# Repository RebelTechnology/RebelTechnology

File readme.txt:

Base repository for Rebel Technology electronics projects.

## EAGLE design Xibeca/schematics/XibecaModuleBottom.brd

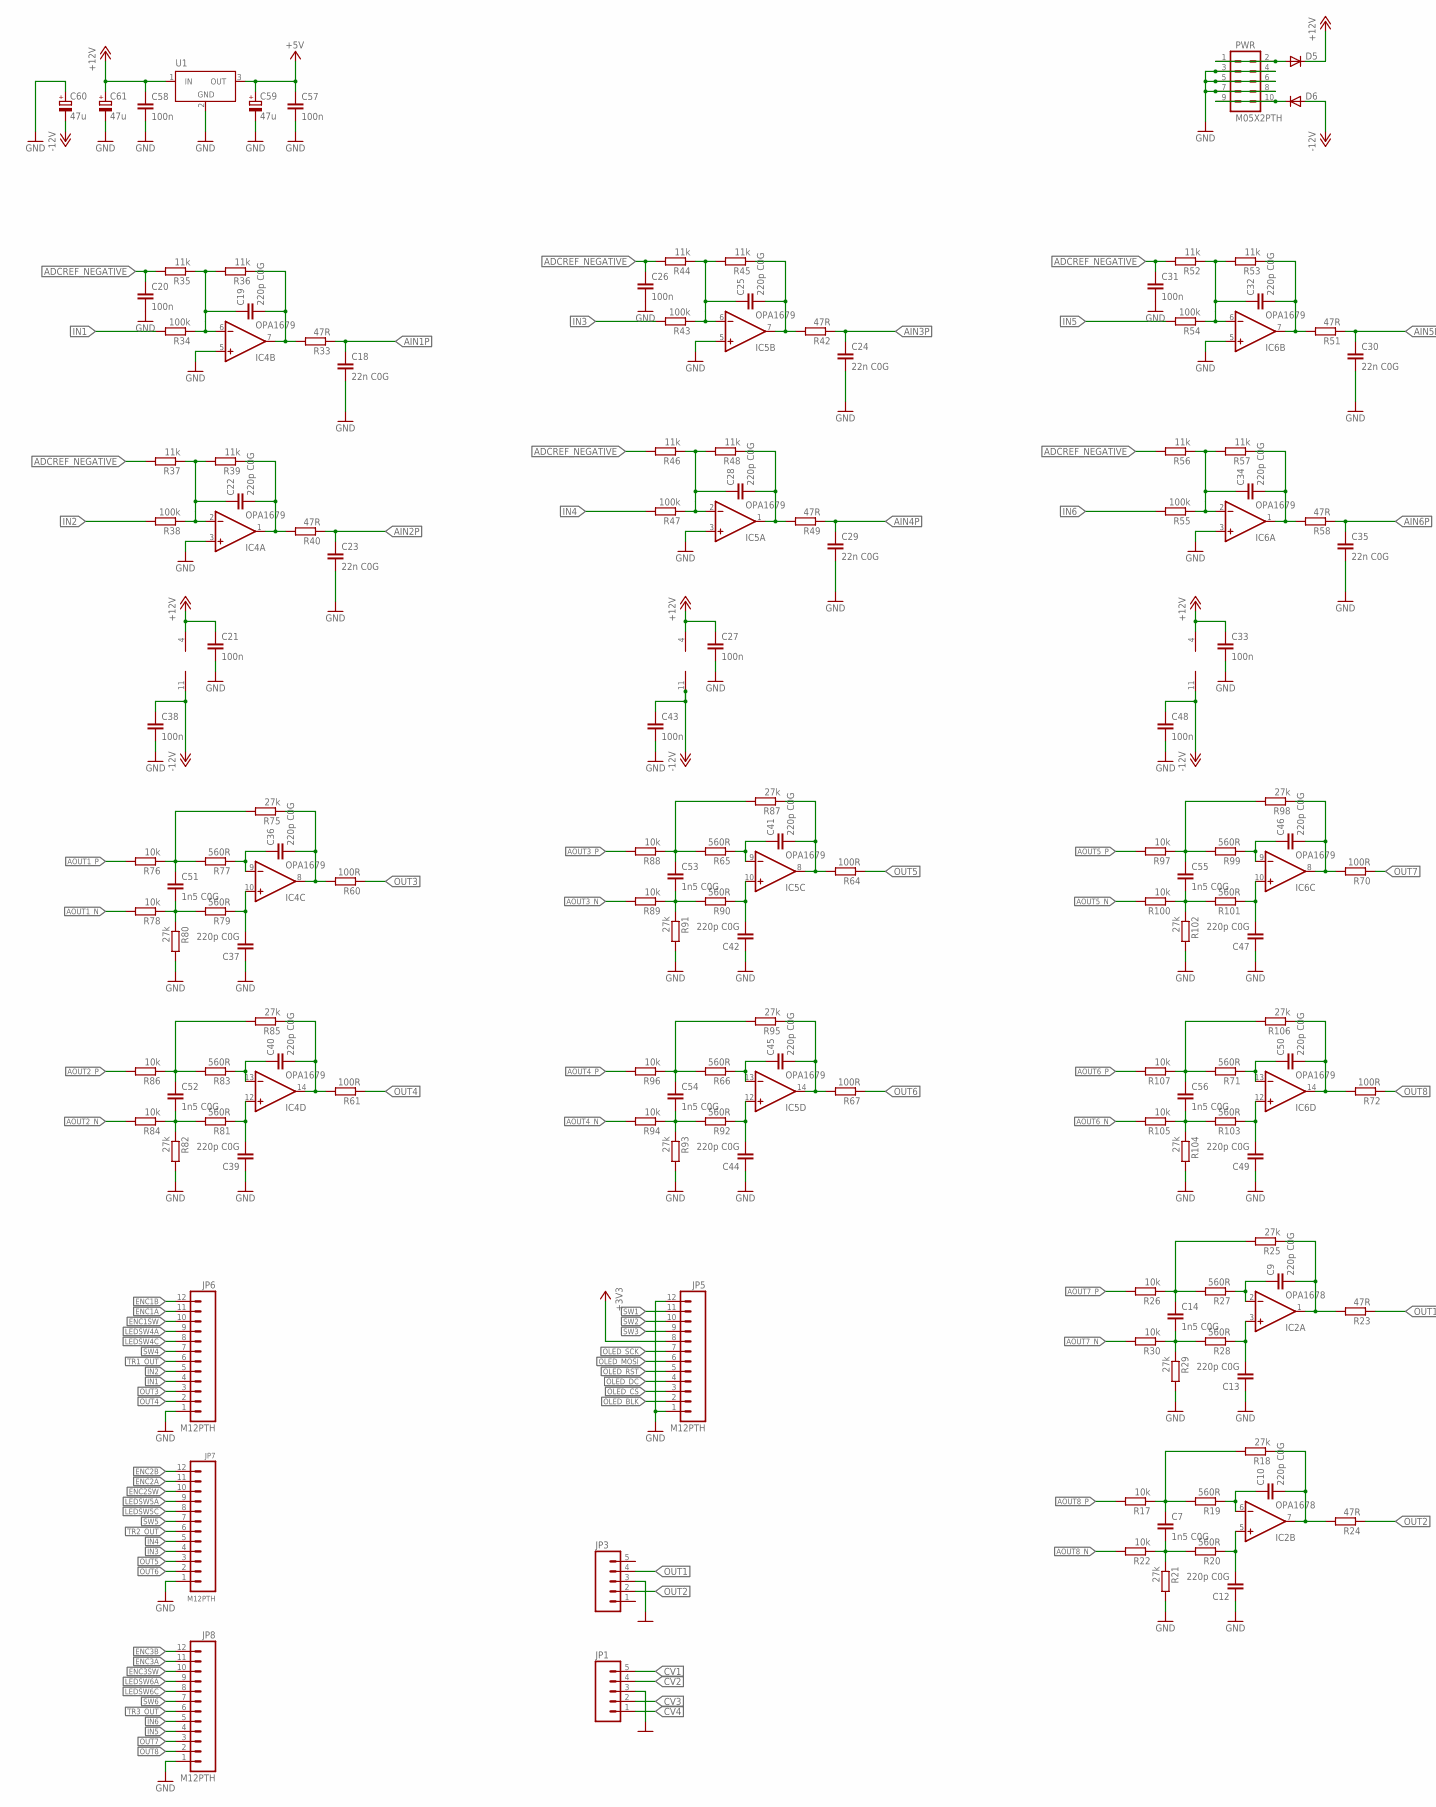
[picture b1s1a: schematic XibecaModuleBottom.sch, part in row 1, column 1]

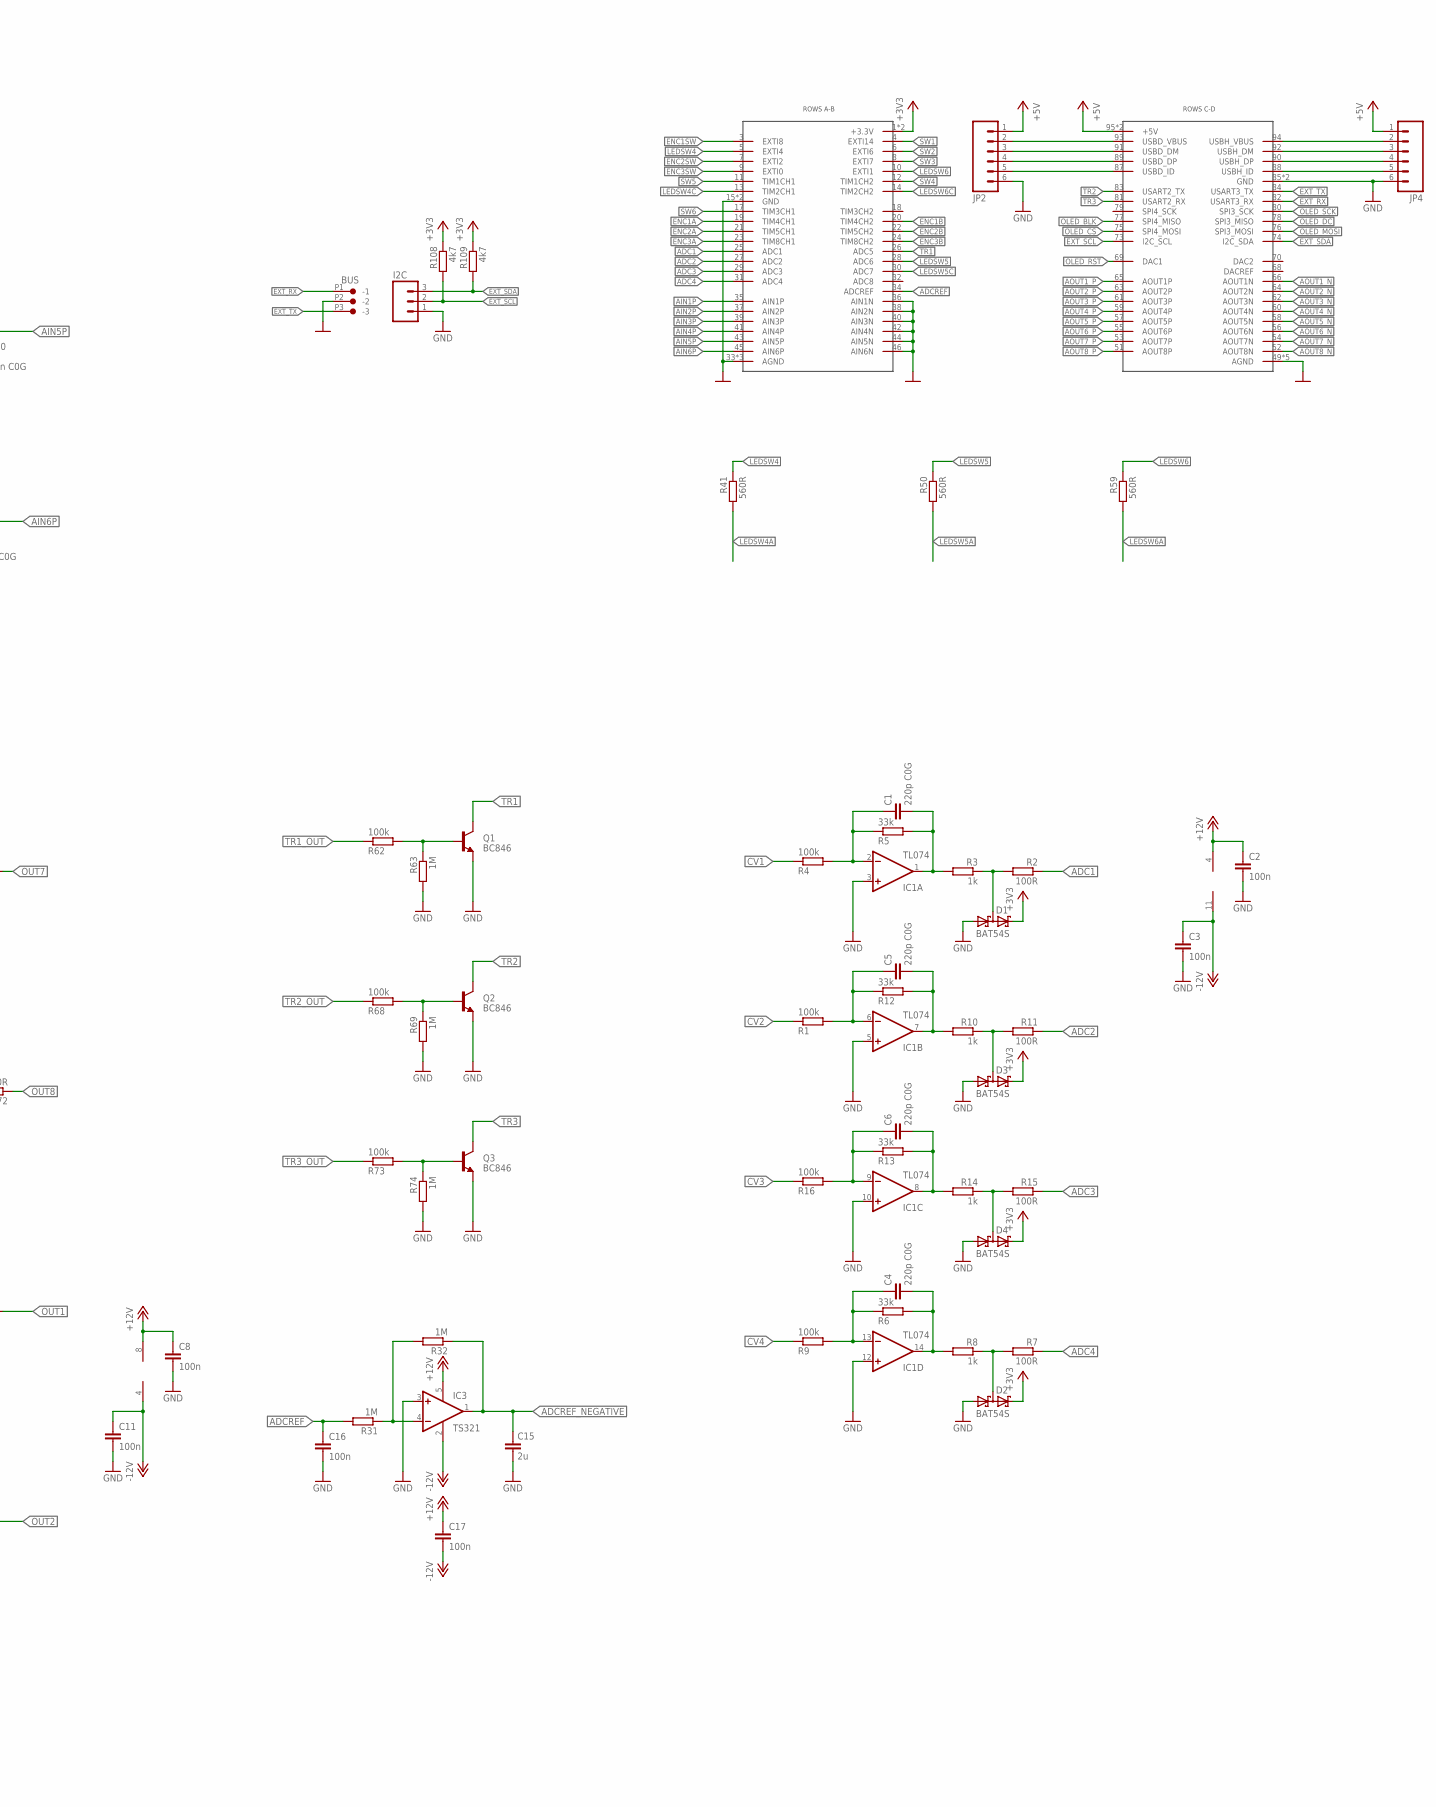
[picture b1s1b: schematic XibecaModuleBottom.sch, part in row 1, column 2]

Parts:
BUS: CON-JST_PH_3W
C1, C4, C5, C6, C9, C10, C12, C13, C19, C22, C25, C28, C32, C34, C36, C37, C39, C40, C41, C42, C44, C45, C46, C47, C49, C50: 220p C0G; C0603
C2, C3, C8, C11, C16, C17, C20, C21, C26, C27, C31, C33, C38, C43, C48, C57, C58: 100n; C0603
C7, C14, C51, C52, C53, C54, C55, C56: 1n5 C0G; C0603
C15: 2u; C0603
C18, C23, C24, C29, C30, C35: 22n C0G; C0603
C59, C60, C61: 47u; E5-8,5
D1, D2, D3, D4: BAT54S; SOT23
D5, D6: DIODE1N4001; DIODE-1N4001
I2C: M03PTH; 1X03
IC1: TL074; SO14
IC2: OPA1678; SO08
IC3: TS321; SOT23-5
IC4, IC5, IC6: OPA1679; SO14
JP1, JP3: M05PTH; 1X05
JP2, JP4: M06SIP; 1X06
JP5, JP6, JP7, JP8: M12PTH; 1X12
PWR: M05X2PTH; AVR_ICSP
Q1, Q2, Q3: BC846; SOT23
R1, R4, R9, R16, R34, R38, R43, R47, R54, R55, R62, R68, R73: 100k; 0603
R2, R7, R11, R15, R60, R61, R64, R67, R70, R72: 100R; 0603
R3, R8, R10, R14: 1k; 0603
R5, R6, R12, R13: 33k; 0603
R17, R22, R26, R30, R76, R78, R84, R86, R88, R89, R94, R96, R97, R100, R105, R107: 10k; 0603
R18, R21, R25, R29, R75, R80, R82, R85, R87, R91, R93, R95, R98, R102, R104, R106: 27k; 0603
R19, R20, R27, R28, R41, R50, R59, R65, R66, R71, R77, R79, R81, R83, R90, R92, R99, R101, R103: 560R; 0603
R23, R24, R33, R40, R42, R49, R51, R58: 47R; 0603
R31, R32, R63, R69, R74: 1M; 0603
R35, R36, R37, R39, R44, R45, R46, R48, R52, R53, R56, R57: 11k; 0603
R108, R109: 4k7; 0603
U1: TSR-1-2450
U$2: NOCTUA2NOCTUA2; NOCTUA

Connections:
+3V3: D1.2 (C2), D2.2 (C2), D3.2 (C2), D4.2 (C2), JP5.8, R108.1, R109.1, U$2.1 (+3.3V), U$2.2 (+3.3V)
+5V: C57.1, C59.+, JP2.1, JP4.1, U1.3 (OUT), U$2.95 (+5V), U$2.96 (+5V)
+12V: C2.1, C8.1, C17.1, C21.1, C27.1, C33.1, C58.1, C61.+, D5.C, IC1.4 (V+), IC2.8 (V+), IC3.5 (V+), IC4.4 (V+), IC5.4 (V+), IC6.4 (V+), U1.1 (IN)
-12V: C3.1, C11.1, C17.2, C38.1, C43.1, C48.1, C60.-, D6.A, IC1.11 (V-), IC2.4 (V-), IC3.2 (V-), IC4.11 (V-), IC5.11 (V-), IC6.11 (V-)
ADC1: R2.1, U$2.25 (ADC1)
ADC2: R11.1, U$2.27 (ADC2)
ADC3: R15.1, U$2.29 (ADC3)
ADC4: R7.1, U$2.31 (ADC4)
ADCREF: C16.1, R31.2, U$2.34 (ADCREF)
ADCREF_NEGATIVE: C15.1, C20.1, C26.1, C31.1, IC3.1 (OUT), R32.1, R35.2, R37.2, R44.2, R46.2, R52.2, R56.2
AIN1P: C18.1, R33.1, U$2.35 (AIN1P)
AIN2P: C23.1, R40.1, U$2.37 (AIN2P)
AIN3P: C24.1, R42.1, U$2.39 (AIN3P)
AIN4P: C29.1, R49.1, U$2.41 (AIN4P)
AIN5P: C30.1, R51.1, U$2.43 (AIN5P)
AIN6P: C35.1, R58.1, U$2.45 (AIN6P)
AOUT1_N: R78.2, U$2.66 (AOUT1N)
AOUT1_P: R76.2, U$2.65 (AOUT1P)
AOUT2_N: R84.2, U$2.64 (AOUT2N)
AOUT2_P: R86.2, U$2.63 (AOUT2P)
AOUT3_N: R89.2, U$2.62 (AOUT3N)
AOUT3_P: R88.2, U$2.61 (AOUT3P)
AOUT4_N: R94.2, U$2.60 (AOUT4N)
AOUT4_P: R96.2, U$2.59 (AOUT4P)
AOUT5_N: R100.2, U$2.58 (AOUT5N)
AOUT5_P: R97.2, U$2.57 (AOUT5P)
AOUT6_N: R105.2, U$2.56 (AOUT6N)
AOUT6_P: R107.2, U$2.55 (AOUT6P)
AOUT7_N: R30.2, U$2.54 (AOUT7N)
AOUT7_P: R26.2, U$2.53 (AOUT7P)
AOUT8_N: R22.2, U$2.52 (AOUT8N)
AOUT8_P: R17.2, U$2.51 (AOUT8P)
CV1: JP1.5, R4.1
CV2: JP1.4, R1.1
CV3: JP1.2, R16.1
CV4: JP1.1, R9.1
ENC1A: JP6.11, U$2.19 (TIM4CH1)
ENC1B: JP6.12, U$2.20 (TIM4CH2)
ENC1SW: JP6.10, U$2.3 (EXTI8)
ENC2A: JP7.11, U$2.21 (TIM5CH1)
ENC2B: JP7.12, U$2.22 (TIM5CH2)
ENC2SW: JP7.10, U$2.7 (EXTI2)
ENC3A: JP8.11, U$2.23 (TIM8CH1)
ENC3B: JP8.12, U$2.24 (TIM8CH2)
ENC3SW: JP8.10, U$2.9 (EXTI0)
EXT_RX: BUS.P1 (-1), U$2.82 (USART3_RX)
EXT_SCL: I2C.2, R108.2, U$2.73 (I2C_SCL)
EXT_SDA: I2C.3, R109.2, U$2.74 (I2C_SDA)
EXT_TX: BUS.P3 (-3), U$2.84 (USART3_TX)
GND: BUS.P2 (-2), C2.2, C3.2, C8.2, C11.2, C12.1, C13.1, C15.2, C16.2, C18.2, C20.2, C21.2, C23.2, C24.2, C26.2, C27.2, C29.2, C30.2, C31.2, C33.2, C35.2, C37.1, C38.2, C39.1, C42.1, C43.2, C44.1, C47.1, C48.2, C49.1, C57.2, C58.2, C59.-, C60.+, C61.-, D1.1 (A1), D2.1 (A1), D3.1 (A1), D4.1 (A1), I2C.1, IC1.3 (+IN), IC1.5 (+IN), IC1.10 (+IN), IC1.12 (+IN), IC3.3 (+IN), IC4.3 (+IN), IC4.5 (+IN), IC5.3 (+IN), IC5.5 (+IN), IC6.3 (+IN), IC6.5 (+IN), JP1.3, JP2.6, JP3.3, JP4.6, JP5.1, JP5.12, JP6.1, JP7.1, JP8.1, PWR.3, PWR.4, PWR.5, PWR.6, PWR.7, PWR.8, Q1.2 (E), Q2.2 (E), Q3.2 (E), R21.2, R29.2, R63.2, R69.2, R74.2, R80.2, R82.2, R91.2, R93.2, R102.2, R104.2, U1.2 (GND), U$2.15 (GND), U$2.16 (GND), U$2.33 (AGND), U$2.36 (AIN1N), U$2.38 (AIN2N), U$2.40 (AIN3N), U$2.42 (AIN4N), U$2.44 (AIN5N), U$2.46 (AIN6N), U$2.47 (AGND), U$2.48 (AGND), U$2.49 (AGND), U$2.50 (AGND), U$2.67 (AGND), U$2.71 (AGND), U$2.72 (AGND), U$2.85 (GND), U$2.86 (GND)
IN1: JP6.4, R34.2
IN2: JP6.5, R38.2
IN3: JP7.4, R43.2
IN4: JP7.5, R47.2
IN5: JP8.4, R54.2
IN6: JP8.5, R55.2
LEDSW4: R41.1, U$2.5 (EXTI4)
LEDSW4A: JP6.9, R41.2
LEDSW4C: JP6.8, U$2.13 (TIM2CH1)
LEDSW5: R50.1, U$2.28 (ADC6)
LEDSW5A: JP7.9, R50.2
LEDSW5C: JP7.8, U$2.30 (ADC7)
LEDSW6: R59.1, U$2.10 (EXTI1)
LEDSW6A: JP8.9, R59.2
LEDSW6C: JP8.8, U$2.14 (TIM2CH2)
unnamed: C40.2, IC4.14 (OUT), R61.2, R85.1
unnamed: C52.2, R81.2, R82.1, R84.1
unnamed: C52.1, R83.2, R85.2, R86.1
unnamed: C22.2, IC4.1 (OUT), R39.1, R40.2
unnamed: C40.1, IC4.13 (-IN), R83.1
unnamed: C22.1, IC4.2 (-IN), R37.1, R38.1, R39.2
unnamed: D6.C, PWR.9, PWR.10
unnamed: C39.2, IC4.12 (+IN), R81.1
unnamed: D5.A, PWR.1, PWR.2
unnamed: C50.2, IC6.14 (OUT), R72.2, R106.1
unnamed: C53.2, R89.1, R90.2, R91.1
unnamed: C53.1, R65.2, R87.2, R88.1
unnamed: C41.1, IC5.9 (-IN), R65.1
unnamed: C42.2, IC5.10 (+IN), R90.1
unnamed: C41.2, IC5.8 (OUT), R64.2, R87.1
unnamed: C45.2, IC5.14 (OUT), R67.2, R95.1
unnamed: C25.2, IC5.7 (OUT), R42.2, R45.1
unnamed: C25.1, IC5.6 (-IN), R43.1, R44.1, R45.2
unnamed: C28.2, IC5.1 (OUT), R48.1, R49.2
unnamed: C28.1, IC5.2 (-IN), R46.1, R47.1, R48.2
unnamed: C46.2, IC6.8 (OUT), R70.2, R98.1
unnamed: C54.2, R92.2, R93.1, R94.1
unnamed: C54.1, R66.2, R95.2, R96.1
unnamed: C45.1, IC5.13 (-IN), R66.1
unnamed: C44.2, IC5.12 (+IN), R92.1
unnamed: IC3.4 (-IN), R31.1, R32.2
unnamed: C9.2, IC2.1 (OUT), R23.2, R25.1
unnamed: C14.2, R28.2, R29.1, R30.1
unnamed: Q1.1 (B), R62.2, R63.1
unnamed: C14.1, R25.2, R26.1, R27.2
unnamed: C10.2, IC2.7 (OUT), R18.1, R24.2
unnamed: C55.2, R100.1, R101.2, R102.1
unnamed: C55.1, R97.1, R98.2, R99.2
unnamed: C46.1, IC6.9 (-IN), R99.1
unnamed: C47.2, IC6.10 (+IN), R101.1
unnamed: C36.2, IC4.8 (OUT), R60.2, R75.1
unnamed: Q2.1 (B), R68.2, R69.1
unnamed: C32.2, IC6.7 (OUT), R51.2, R53.1
unnamed: C32.1, IC6.6 (-IN), R52.1, R53.2, R54.1
unnamed: C34.2, IC6.1 (OUT), R57.1, R58.2
unnamed: C34.1, IC6.2 (-IN), R55.1, R56.1, R57.2
unnamed: C56.2, R103.2, R104.1, R105.1
unnamed: C56.1, R71.2, R106.2, R107.1
unnamed: C50.1, IC6.13 (-IN), R71.1
unnamed: C49.2, IC6.12 (+IN), R103.1
unnamed: C5.1, IC1.6 (-IN), R1.2, R12.1
unnamed: C1.1, IC1.2 (-IN), R4.2, R5.1
unnamed: Q3.1 (B), R73.2, R74.1
unnamed: C9.1, IC2.2 (-IN), R27.1
unnamed: C13.2, IC2.3 (+IN), R28.1
unnamed: C7.2, R20.2, R21.1, R22.1
unnamed: C7.1, R17.1, R18.2, R19.2
unnamed: C10.1, IC2.6 (-IN), R19.1
unnamed: C12.2, IC2.5 (+IN), R20.1
unnamed: C1.2, IC1.1 (OUT), R3.2, R5.2
unnamed: D1.3 (C1A2), R2.2, R3.1
unnamed: C5.2, IC1.7 (OUT), R10.2, R12.2
unnamed: D3.3 (C1A2), R10.1, R11.2
unnamed: C6.1, IC1.9 (-IN), R13.1, R16.2
unnamed: C6.2, IC1.8 (OUT), R13.2, R14.2
unnamed: D4.3 (C1A2), R14.1, R15.2
unnamed: C4.1, IC1.13 (-IN), R6.1, R9.2
unnamed: C4.2, IC1.14 (OUT), R6.2, R8.2
unnamed: D2.3 (C1A2), R7.2, R8.1
unnamed: JP2.2, U$2.93 (USBD_VBUS)
unnamed: JP2.3, U$2.91 (USBD_DM)
unnamed: JP2.4, U$2.89 (USBD_DP)
unnamed: JP2.5, U$2.87 (USBD_ID)
unnamed: JP4.5, U$2.88 (USBH_ID)
unnamed: JP4.4, U$2.90 (USBH_DP)
unnamed: JP4.3, U$2.92 (USBH_DM)
unnamed: JP4.2, U$2.94 (USBH_VBUS)
unnamed: C51.2, R78.1, R79.2, R80.1
unnamed: C51.1, R75.2, R76.1, R77.2
unnamed: C36.1, IC4.9 (-IN), R77.1
unnamed: C37.2, IC4.10 (+IN), R79.1
unnamed: C19.2, IC4.7 (OUT), R33.2, R36.1
unnamed: C19.1, IC4.6 (-IN), R34.1, R35.1, R36.2
OLED_BLK: JP5.2, U$2.77 (SPI4_MISO)
OLED_CS: JP5.3, U$2.75 (SPI4_MOSI)
OLED_DC: JP5.4, U$2.78 (SPI3_MISO)
OLED_MOSI: JP5.6, U$2.76 (SPI3_MOSI)
OLED_RST: JP5.5, U$2.69 (DAC1)
OLED_SCK: JP5.7, U$2.80 (SPI3_SCK)
OUT1: JP3.4, R23.1
OUT2: JP3.2, R24.1
OUT3: JP6.3, R60.1
OUT4: JP6.2, R61.1
OUT5: JP7.3, R64.1
OUT6: JP7.2, R67.1
OUT7: JP8.3, R70.1
OUT8: JP8.2, R72.1
SW1: JP5.11, U$2.4 (EXTI14)
SW2: JP5.10, U$2.6 (EXTI6)
SW3: JP5.9, U$2.8 (EXTI7)
SW4: JP6.7, U$2.12 (TIM1CH2)
SW5: JP7.7, U$2.11 (TIM1CH1)
SW6: JP8.7, U$2.17 (TIM3CH1)
TR1: Q1.3 (C), U$2.26 (ADC5)
TR1_OUT: JP6.6, R62.1
TR2: Q2.3 (C), U$2.83 (USART2_TX)
TR2_OUT: JP7.6, R68.1
TR3: Q3.3 (C), U$2.81 (USART2_RX)
TR3_OUT: JP8.6, R73.1

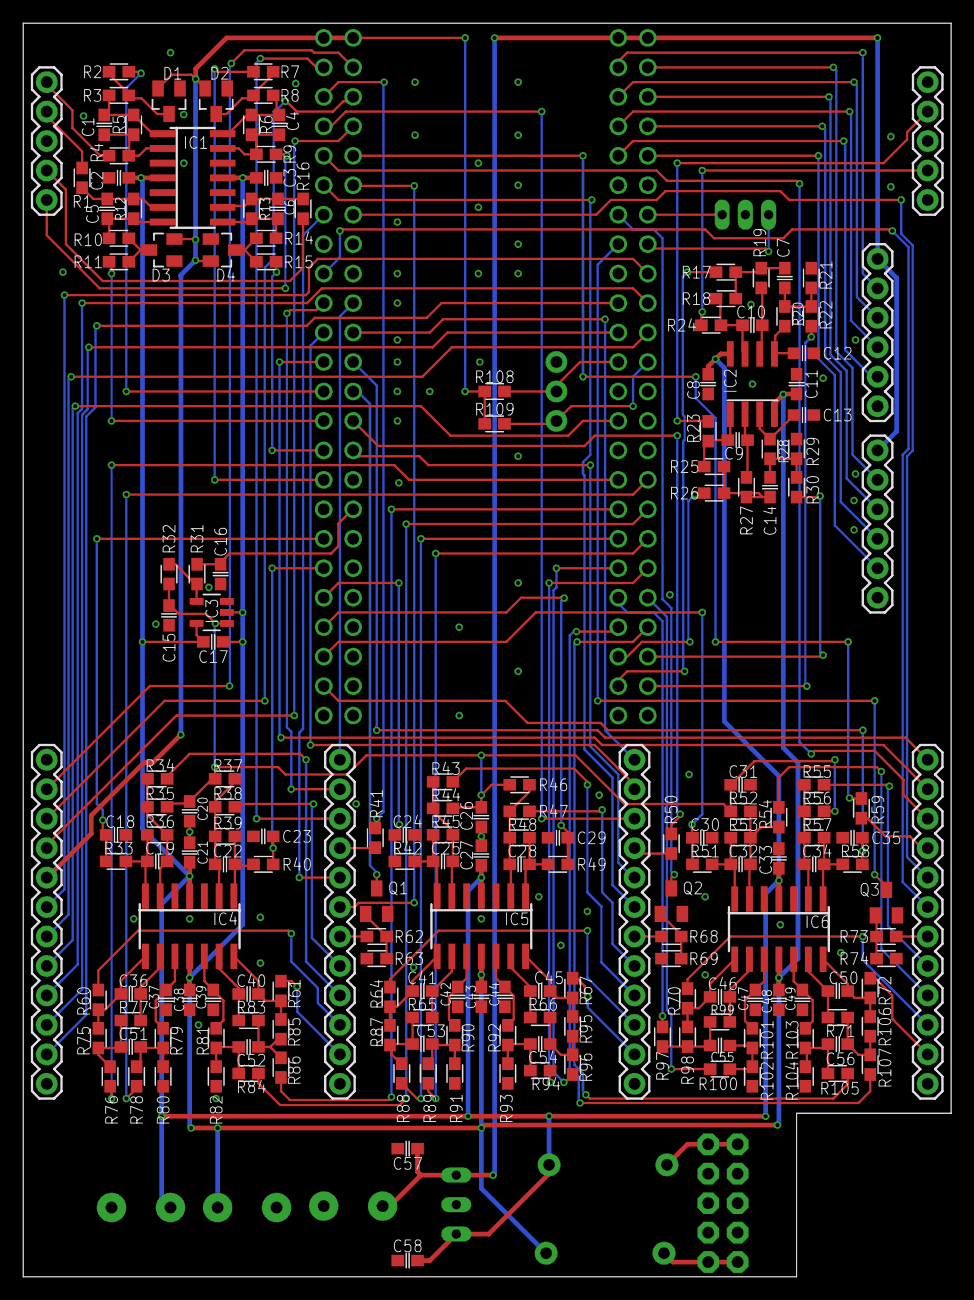
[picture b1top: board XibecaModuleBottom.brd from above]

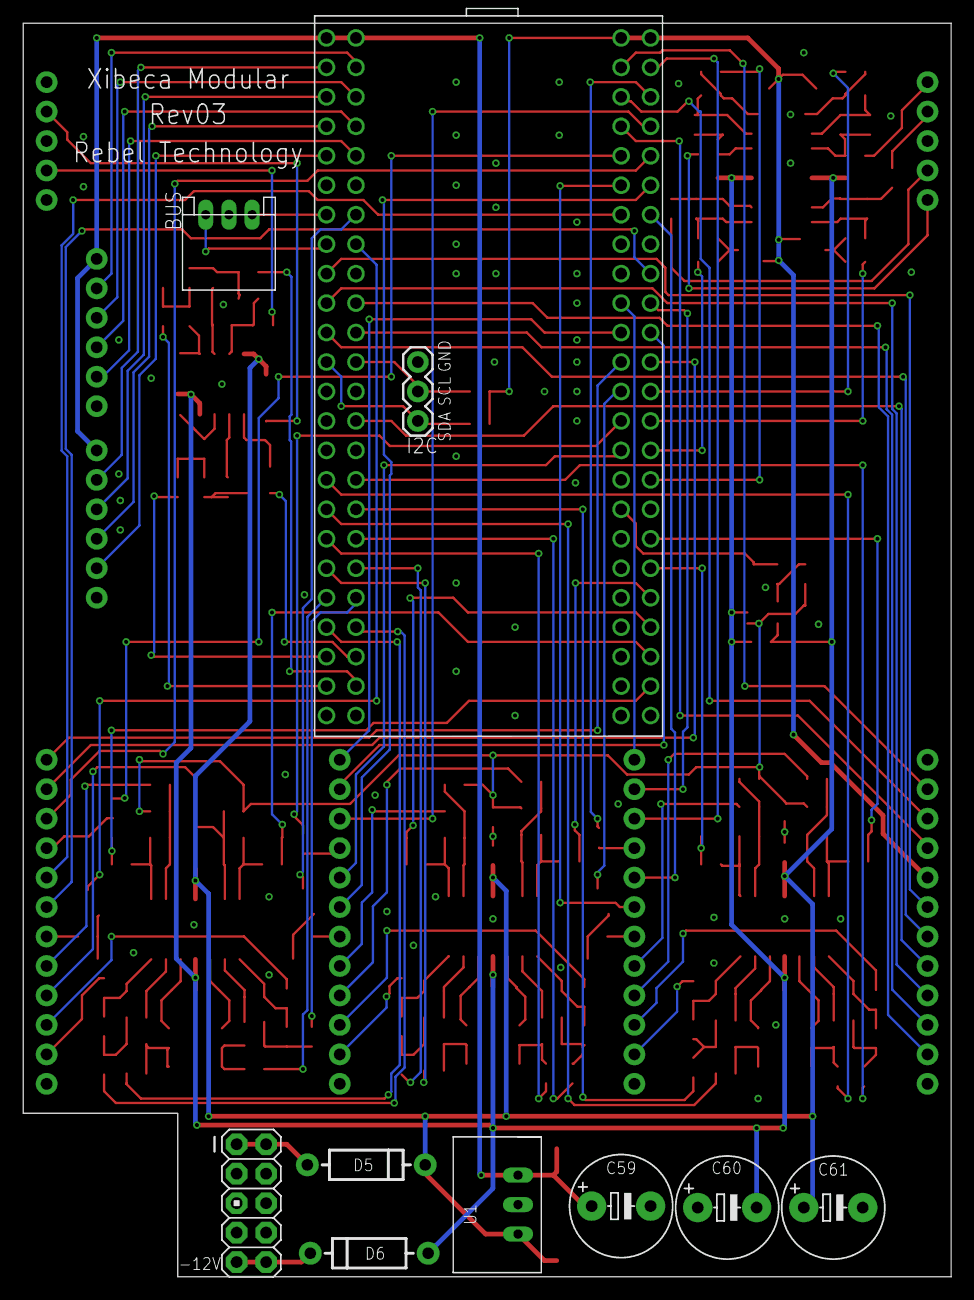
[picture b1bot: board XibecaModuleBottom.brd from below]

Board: 2 copper layers, 80.0 x 108.1 mm, 198 parts (10 on the bottom side), 169 nets.

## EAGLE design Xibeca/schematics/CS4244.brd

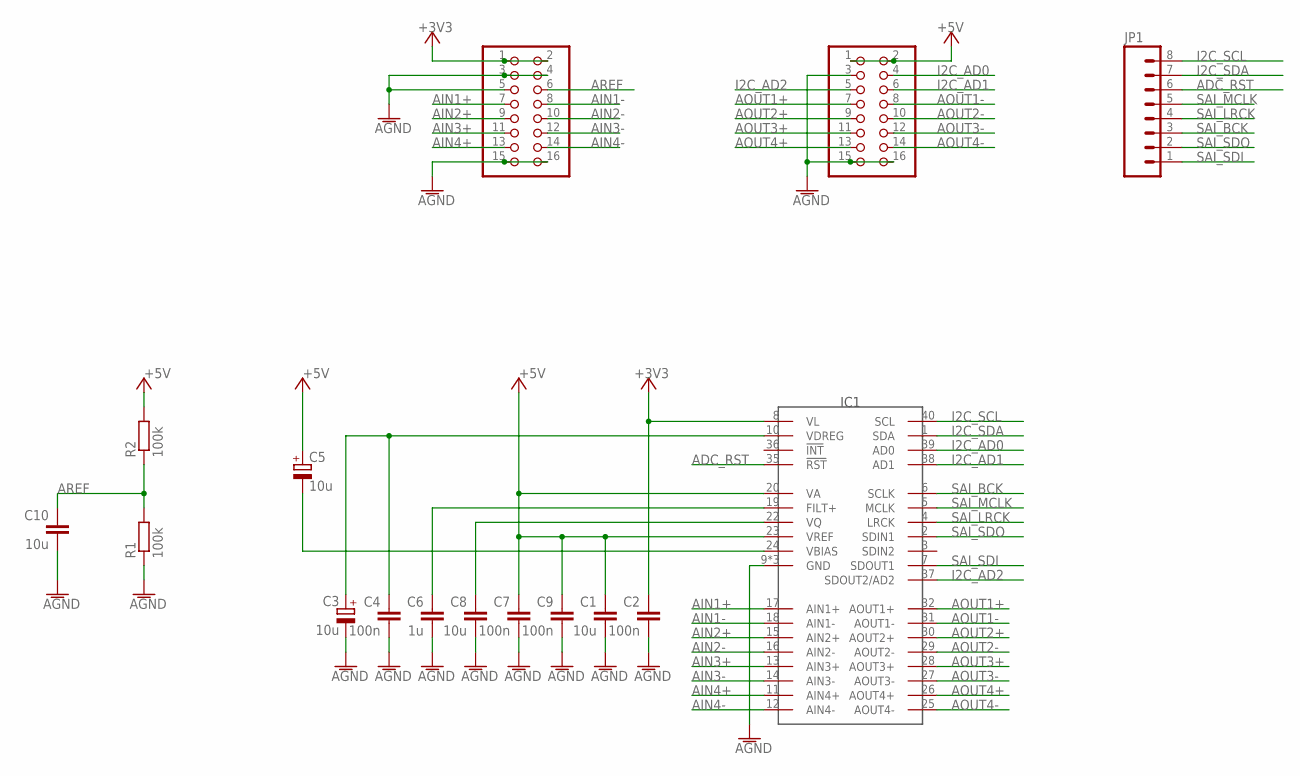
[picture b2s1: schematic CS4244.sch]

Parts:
C1, C8, C10: 10u; C0603
C2, C4, C7, C9: 100n; C0603
C3, C5: 10u; UD-4X5,8_NICHICON
C6: 1u; C0603
IC1: CS4244; QFN50P600X600X100-41N
JP1: M081X08; 1X08
JP2, JP3: PINHD-2X8; 2X08
R1, R2: 100k; 0603

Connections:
+3V3: C2.1, IC1.8 (VL), JP2.1, JP2.2
+5V: C1.1, C5.+, C7.1, C9.1, IC1.20 (VA), IC1.23 (VREF), JP3.1, JP3.2, R2.2
ADC_RST: IC1.35 (!RST), JP1.6
AGND: C1.2, C2.2, C3.-, C4.2, C6.2, C7.2, C8.2, C9.2, C10.2, IC1.9 (GND), IC1.21 (GND), IC1.41 (GND), JP2.3, JP2.4, JP2.5, JP2.15, JP2.16, JP3.3, JP3.15, JP3.16, R1.1
AIN1+: IC1.17 (AIN1+), JP2.7
AIN1-: IC1.18 (AIN1-), JP2.8
AIN2+: IC1.15 (AIN2+), JP2.9
AIN2-: IC1.16 (AIN2-), JP2.10
AIN3+: IC1.13 (AIN3+), JP2.11
AIN3-: IC1.14 (AIN3-), JP2.12
AIN4+: IC1.11 (AIN4+), JP2.13
AIN4-: IC1.12 (AIN4-), JP2.14
AOUT1+: IC1.32 (AOUT1+), JP3.7
AOUT1-: IC1.31 (AOUT1-), JP3.8
AOUT2+: IC1.30 (AOUT2+), JP3.9
AOUT2-: IC1.29 (AOUT2-), JP3.10
AOUT3+: IC1.28 (AOUT3+), JP3.11
AOUT3-: IC1.27 (AOUT3-), JP3.12
AOUT4+: IC1.26 (AOUT4+), JP3.13
AOUT4-: IC1.25 (AOUT4-), JP3.14
AREF: C10.1, JP2.6, R1.2, R2.1
I2C_AD0: IC1.39 (AD0), JP3.4
I2C_AD1: IC1.38 (AD1), JP3.6
I2C_AD2: IC1.37 (SDOUT2/AD2), JP3.5
I2C_SCL: IC1.40 (SCL), JP1.8
I2C_SDA: IC1.1 (SDA), JP1.7
unnamed: C5.-, IC1.24 (VBIAS)
unnamed: C3.+, C4.1, IC1.10 (VDREG)
unnamed: C6.1, IC1.19 (FILT+)
unnamed: C8.1, IC1.22 (VQ)
SAI_BCK: IC1.6 (SCLK), JP1.3
SAI_LRCK: IC1.4 (LRCK), JP1.4
SAI_MCLK: IC1.5 (MCLK), JP1.5
SAI_SDI: IC1.7 (SDOUT1), JP1.1
SAI_SDO: IC1.2 (SDIN1), JP1.2

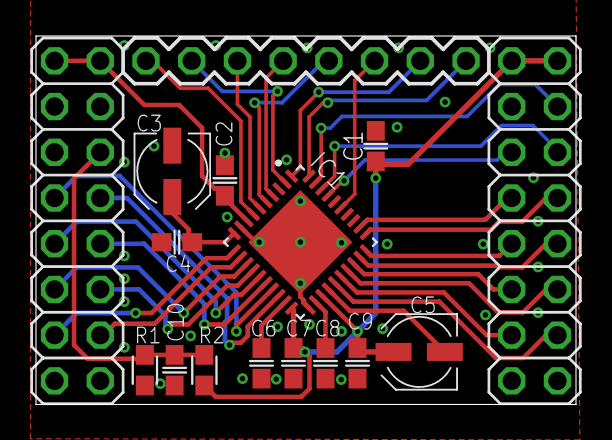
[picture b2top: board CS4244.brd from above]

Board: 2 copper layers, 30.0 x 20.5 mm, 16 parts (0 on the bottom side), 35 nets.

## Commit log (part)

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2018-08-14 changed op amp value to TS974
2018-08-14 changed op amp to TS974 and vreg to LM7805
2018-08-28 changed colours
2018-08-28 renamed SW5 network
2018-08-28 Rev06 updates: simplified labels and added mounting holes. Increased some component spacing.
2018-08-29 swapped USB HS and FS
2018-08-31 big speaker version
2018-08-31 added speaker grille
2018-08-31 fixed grille error
2018-08-31 changed side feet to be same height
2018-08-31 added grille to small version
2018-08-31 added light pipe
2018-08-31 updated notes
2018-08-31 fixed back piece
2018-09-06 updated drawings and notes
2018-09-06 Fixed front cut-out
2018-09-06 added lightpipe
2018-09-13 added logo
2018-09-26 paper designs
2018-10-01 added label to schematic
2018-10-01 updated and added labels
2018-10-01 removed comments
2018-10-01 renamed ENC2_SW1 network ENC2_SW
2018-10-04 updated drawings with 15mm LED
2018-10-04 Rev03
2018-10-09 DXF sent to Mark
2018-10-09 updated drawings
2018-10-12 draft version of modular wizard
2018-10-12 created OWL2-H cube file
2018-10-15 added expander and connectors templates
2018-10-15 index on master: 50de6d9d added expander and connectors templates
2018-10-18 first draft of circuit and PCB arrangement. Need to assign pins for Mode switch
2018-10-22 rev03: moved back USBH connector
2018-10-23 added design, moved LED
2018-10-23 moved LED, changed button assignment
2018-10-23 eurorack design updates
2018-10-28 First draft of BioSignals schematic
2018-10-29 design adjustments
2018-10-29 notes
2018-10-29 Completed first version of Wizard Eurorack PCB
2018-11-04 adjusted
2018-11-04 added 100nF to NRST
2018-11-17 added accelerometer to schematic and updated cube file
2018-11-19 added barcode
2018-12-12 adjusted placing and labels
2018-12-12 renamed EuroWizard
2018-12-12 changed 4k3 resistors to 4k7
2018-12-12 added Manifold schematics
2018-12-22 manifold/wavetable updates
2018-12-22 change resistor value
2018-12-24 Magus Expander Rev02 : swapped usb host/device, changed to electrolytic USBH VBUS cap
2018-12-24 changed to 47u USBH VBUS cap
2018-12-26 saved in v7 format
2019-01-09 aligned to new cut-outs from Mark's dxf, changed to 'USB A' and 'USB B' labels
2019-01-23 added cube file for Noctua small OWL dev board
2019-02-11 Started Noctua design and rough arrangement. Need to finish assigning pins to ADC and MCU
2019-02-12 some routing around MCU to finish and ADC serial connections to add
2019-02-19 Most tracking complete. Only 2 SPI control lines left to add
2019-02-19 Completed first draft of layout for review
2019-02-19 Tidied some tracks
2019-02-20 added extra connections for LRCK and BCK to codec
2019-02-21 updated for publishing schematics
2019-02-21 Magus Rev03 production
2019-02-21 added notes
2019-02-21 Magus Rev03
2019-02-21 added TLC5946
2019-02-21 MagusConnectors Rev04 production
2019-02-21 side panel for 3mm frost black perspex cut
2019-02-21 added lumberg jacks
2019-02-21 added tant caps to ICL7660 and film caps to audio in
2019-02-21 changed to polarised tant cap footprints
2019-02-26 packaging labels for Magus Eurorack edition
2019-03-04 changed 47u cap package, changed value naming style
2019-03-04 SAI changes
2019-03-04 added logo and labels on back
2019-03-06 updated electrolyic cap packages and streamlined values, updated LED parts
2019-03-06 Rev06 with SIP dc/dc converter footprint
2019-03-06 fixed stray milling line in DC jack
2019-03-08 layer changes
2019-03-08 moved OWL Pedal files
2019-04-11 fixed audio wire error
2019-04-11 added +5v power plane for LEDs, added top layer ground plane, added ground stitching, connected AUDIO_OUT ground pin
2019-04-11 Magus Rev05
2019-04-16 changed board width to 25mm. Rev07.
2019-04-16 adjusted wire
2019-04-19 draft OWL Pedal mkII designs
2019-04-26 side panel for CNC
2019-04-26 updated USB names and fixed a resistor value
2019-06-13 board to hold oled screen
2019-06-13 added mounting holes for screen board
2019-06-13 removed bottom hole and slot
2019-07-12 added STM32F446 to library
2019-08-02 added docs and notes
2019-08-02 updated packages and set Rev07
2019-08-02 added BF861ABC
2019-09-05 updated corners (tracing 2mm out from regular panel)
2019-09-05 oled screen plastic protector
2019-09-23 Magus labels, desktop version
2019-09-23 labels for Wizard
2019-09-24 Rev 06
2019-09-27 routed
2019-09-27 added bypass header
2019-09-27 changed to smt bypass components
2019-09-27 touched up placement and finalised routing
2019-09-27 changed labels
2019-11-07 changed to op amp TS924
2019-12-12 updated to Rev03 with stereo-thonkiconn
2019-12-30 changed op amp part to TS924
2020-02-02 updated shipping labels to new format and added barcode
2020-02-05 changed electrolytic capacitor footprints and values, changed vreg to TLV1117
2020-02-05 removed wire stub, changed to Rev02
2020-02-05 specified op amps as TL074
2020-02-05 rotated power inlet, changed to TO220 regulator, changed some routing
2020-02-05 straightened out
2020-02-07 updated labels to new inkscape format
2020-02-19 DIY standalone Wizard
2020-02-25 vector font
2020-02-25 layout and through hole components
2020-02-26 Witch is not Wizard
2020-03-03 witch updates
2020-03-04 moved Witch to its own project directory
2020-03-06 changed 37k resistors to 36k
2020-03-06 changed op amp to OPA1648
2020-04-02 updated capacitor footprints and values
2020-04-02 Added 5v regulator. Moved pots 0.0125in to edge. Reduced depth. Rev05.
2020-04-02 changed some component values
2020-06-04 updated spacing for new Inkscape format
2020-06-08 outstanding commits
2020-06-08 James Nesfield's night light project
2020-06-12 adaptor board for Digilent Analog Discovery 2
2020-06-13 added V+/GND/V- header, labels
2020-06-18 updated to new inkscape format
2020-06-18 pdf version
2020-06-21 draft usb euro-power utility board
2020-06-21 added dc converter parts
2020-07-08 updated design for board rev01
2020-07-13 cut rev 2
2020-09-15 moved/added Fahrion panel proofs
2020-09-15 moved Fahrion proof
2020-10-02 packaging labels
2020-10-07 labels for shipping Logoi
2020-10-13 changed component values to match Magus
2020-10-13 turned OLED ffc connector around and moved uart and swd headers
2020-10-14 genius updates
2020-10-15 genius changes
2020-10-15 added interconnect pins, moved MIC2005 to bottom, added USBD ESD filter, routed top board and changed components to PTH
2020-10-15 bottom board routed
2020-10-16 changed 22u cap to 1u film
2020-10-16 stiching, layout and labels
2020-10-16 tidy before changing vias
2020-10-16 fixed blind vias, changed design rules and fixed clearance
2020-10-16 labels
2020-10-17 moved CV input voltage divider
2020-10-17 separated SW and TR_IN
2020-10-17 changed OLED_MOSI pin to match cube setup
2020-10-17 Player renamed Genius
2020-10-17 drawings and notes changes
2020-10-20 Rev01 sent for manufacture
2020-10-20 changed board width to 29.8mm and moved trimpots away from switches. changed switch footprint to round pads.
2020-10-20 Voltage divider on tuning level. Rev05.
2020-10-20 Added 5v regulator. Rev07
2020-10-20 USB power adaptor Rev01
2020-10-26 wire changes
2020-10-28 updated to new format
2020-11-01 STM32H7 version of Noctua
2020-11-27 Genius Rev02
2020-11-27 changed BOOT0 pull down to 10k (was 22R)
2021-01-06 added back line drawing
2021-01-06 added dc jack and line drawing clip
2021-01-07 move lid outline and holes 1mm north
2021-01-07 pixi owl wip
2021-01-08 routed pixi analog
2021-01-08 routed pixi spi
2021-01-08 assignemnts and routing complete
2021-01-09 routing updates
2021-01-09 swapped PC4 for PB0
2021-01-09 added pin labels
2021-01-13 centred programming header
2021-01-14 changed vreg to switching TSR Traco
2021-01-22 label changes
2021-01-22 mocked up with screen and encoder
2021-01-22 update toolroot
2021-01-22 Rotated leds. Changed label to Rev02
2021-01-22 renamed files
2021-01-26 ClockMultiplier renamed Phoreo
2021-01-26 Added 5V regulator. Phoreo Rev04.
2021-01-28 Added new Noctua cube file
2021-01-28 Updated pin headers and udpated tracking around codec and analogue pins
2021-01-28 Tidied tracking around power supply
2021-01-28 added SDRAM datasheet
2021-01-29 Added new RAM IC and connected power rails to STM & RAM
2021-01-29 Updated board placements
2021-02-05 RAM and FLASH added and wired into STM. Rough layout complete
2021-02-05 pushed again after a save
2021-02-16 tracked more of RAM and completed Flash
2021-02-27 Updated pin peripheral mappings
2021-02-27 Sorted external connections and tracked right hand side header
2021-02-28 tracked all analogue parts to STM
2021-03-01 Revert "Updated cube file"
    This reverts commit f77cf304d45f6124e2a472ca2469904ed4213c9a.
2021-03-02 Checked all pin assignments to RAM & STM and updated cube file
2021-03-02 All RAM tracks brought up to STM
2021-03-03 Completed routing RAM
2021-03-03 Board tidied and wire stubs removed
2021-03-03 Updated cube file pin assignments after tracking completed
2021-03-03 tidied idents - board complete
2021-03-03 fixed Airwire missed by DRC
2021-03-03 rearranged
2021-03-03 notes and top adjustments
2021-03-03 fix label
2021-03-03 changed to TO-92 vreg. Rev08
2021-03-03 changed routing to access I2C
2021-03-03 minor adjustments
2021-03-03 removed unused layers
2021-03-03 routing complete
2021-03-04 Xibeca renamed Noctua2
2021-03-04 Noctua v2 renamed Xibeca
2021-03-04 changed boot0 pull-down from 22R to 10k
2021-03-04 changed C12 to 0603, changed C21 to 0402
2021-03-04 fixed labels
2021-03-08 added cube file for Noctua with H7 processor
2021-03-08 Updated pin header mapping to match Xibeca
2021-03-08 deleted tracks that need to be re-routed and tracked around ADC
2021-03-09 Updated Noctua2 cube file to match schematic
2021-03-09 Schematic complete
2021-03-09 tracking complete
2021-03-09 swapped SAI in and out channels to match Noctua
2021-03-11 removed 100n 16v spec
2021-03-11 removed soldermask 12v label from back
2021-03-11 Noctua renamed Noctua1
2021-03-12 OwlPedal2 Rev02
2021-03-12 changed labels, Noctua2 Rev01
2021-03-12 routing, labels, moved headers to bottom
2021-03-12 ClockDelay renamed Logoi
2021-03-12 EuclideanSequencer renamed and split into Stocheia and Klasmata project folders
2021-03-12 Added vreg TO-92. Rev06
2021-03-12 Added vreg TO-92. Rev05
2021-03-12 renamed CLK
2021-03-12 fixed -12v label
2021-03-17 Changed to PJ302M jacks. Rev07.
2021-03-17 changed jack route width to 0
2021-03-17 increased pad size on STM to 0.3mm and cleared all DRC errors
2021-03-17 PCB updated and ready for production
2021-03-17 stereo jack update
2021-04-02 MIDI expansion for lich/genius
2021-04-06 updated CLK designs, separated jacks to fit LEDs, changed jack slots
2021-04-07 CLK Rev08
2021-05-31 Routing updated, changed to 47uF 5mm caps, Rev03
2021-06-04 TapTempo renamed Chronos
2021-06-04 replaced Chronos with TapTempoMk2
2021-06-04 Increased cap size to 5mm 47uF. Added logo. Rev07.
2021-07-08 Renumbered
2021-07-08 renamed
2021-07-08 part renamed/dnp
2021-07-08 eagle version change
2021-07-09 added labels
2021-09-01 new version of ToggleTone, renamed Root
2021-09-03 analog toggling tonic
2021-09-13 OWL Pedal mkII Rev03
2021-09-13 Moved parts and rerouted. Rev01
2021-09-21 moved adapter designs
2021-09-23 created screen holder part
2021-09-23 top Rev03 files
2021-10-06 updated with MIC2005 switch, routed Rev01
2021-10-06 adjusted labels
2021-10-06 Analog Switch Bypass Rev01
2021-10-08 wip 12HP Xibeca Eurorack module with 2 or 1.54 inch TFT screen
2021-10-16 Rev04
2021-10-19 added middle board and some headers
2021-10-27 added midi tx PNP buffer and encoder filtering caps
2021-11-02 fixed disconnected 3-pin header position
2021-11-11 changed input and output filters
2021-11-11 Renumbered parts. Rev02.
2021-11-11 added I2C bus
2021-11-15 draft versions of Xibeca
2021-11-16 routed CS4244 breakout
2021-11-25 widened USB 1mm, shifted pushbutton holes 25mil north
2021-11-27 connections and arrangement, fixed audio circuits
2021-12-15 changed 480pF to 470pF
2021-12-15 show orientation on diode footprint
2021-12-15 notes and panel changes
2021-12-15 smashed name
2022-01-08 placement and started routing
2022-01-08 routing wip
2022-01-14 labels, bom, changed LM321 supply back to 5V
2022-01-14 changed single op amp to TS321. Rev03.

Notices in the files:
parts and their libraries:
SparkFun: Licensing: CC v3.0 Share-Alike You are welcome to use this library for commercial purposes.
SparkFun-Connectors: Licensing: Creative Commons ShareAlike 4.0 International - https://creativecommons.org/licenses/by-sa/4.0
